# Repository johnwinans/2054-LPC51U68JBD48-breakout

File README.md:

# 2054-LPC51U68JBD48-breakout
LPC51U68JBD48 Breakout Board

Oops... I put the wrong URL on the Rev-1 release tag.  You can order Rev 1 of this board from OSH Park here: https://oshpark.com/shared_projects/a4fI5XNS (I receive no commission.)

Double-oops, there is no soldermask threaded between the pins of U1 in Rev-1.  This flaw is not a show-stopper.  It would have been nice to have.  

This has been fixed by reducing the solder mask expansion in Rev 1.1 to 1.8 mils.

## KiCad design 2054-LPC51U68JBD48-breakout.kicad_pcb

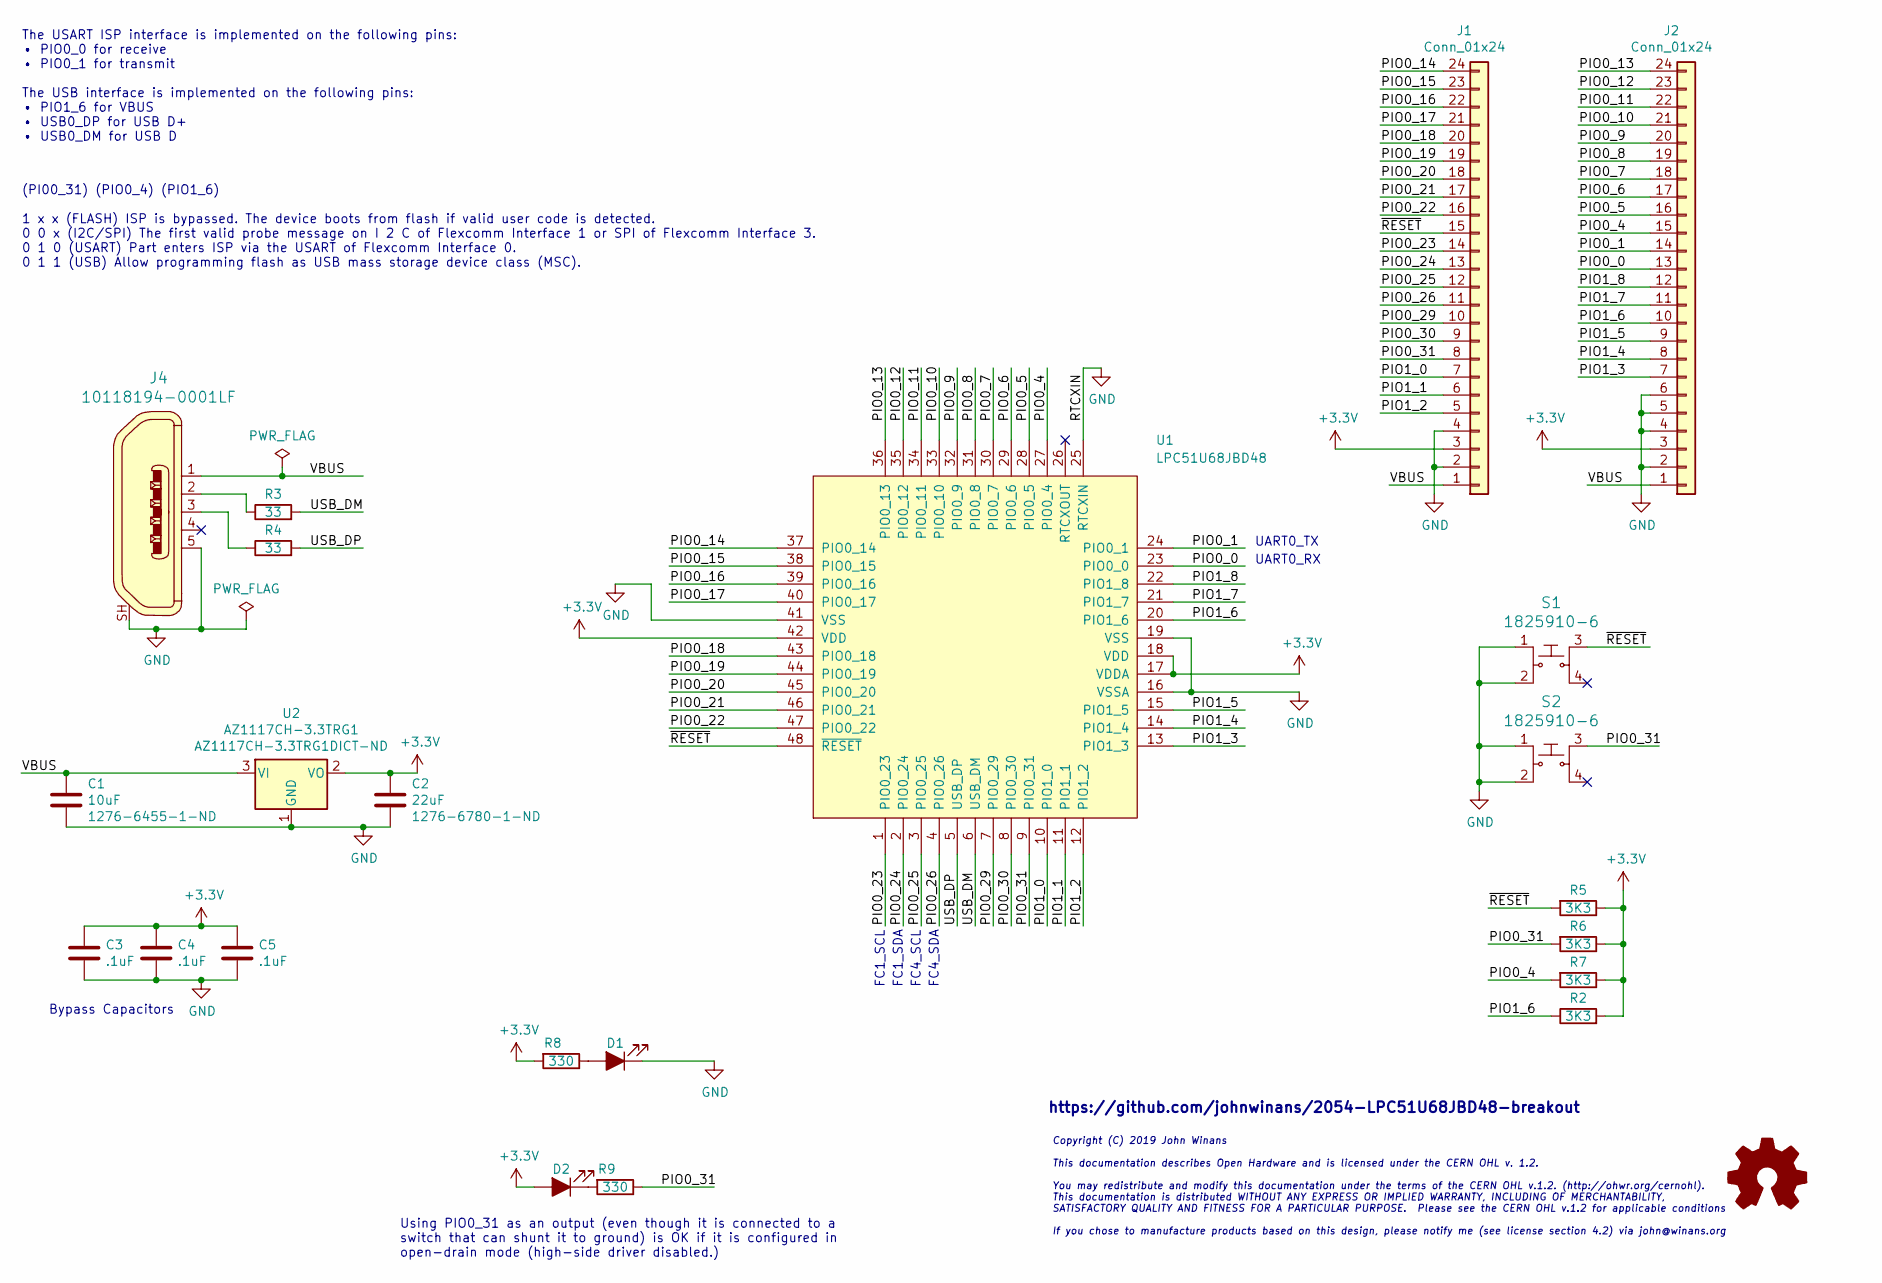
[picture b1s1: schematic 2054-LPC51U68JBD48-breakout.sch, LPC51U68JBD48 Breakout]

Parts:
C1: 10uF; C_0805_2012Metric_Pad1.15x1.40mm_HandSolder; digikey 1276-6455-1-ND
C2: 22uF; C_0805_2012Metric_Pad1.15x1.40mm_HandSolder; digikey 1276-6780-1-ND
C3, C4, C5: .1uF; C_0603_1608Metric_Pad1.05x0.95mm_HandSolder; digikey.com 445-6854-1-ND
D1, D2: LED_ALT; LED_0603_1608Metric_Pad1.05x0.95mm_HandSolder
J1, J2: Conn_01x24; PinHeader_1x24_P2.54mm_Vertical
J4: 10118194-0001LF; USB_Micro_B_Female_10118194-0001LF; MPN 10118194-0001LF; Digi-Key_PN 609-4618-1-ND
LOGO1: Logo_Open_Hardware_Small; OSHW-Symbol_6.7x6mm_SilkScreen
R2, R5, R6, R7: 3K3; R_0603_1608Metric_Pad1.05x0.95mm_HandSolder; digikey.com 311-100HRCT-ND
R3, R4: 33; R_0603_1608Metric_Pad1.05x0.95mm_HandSolder; digikey.com 311-100HRCT-ND
R8, R9: 330; R_0603_1608Metric_Pad1.05x0.95mm_HandSolder; digikey.com 311-1.00KHRCT-ND
S1, S2: 1825910-6; Switch_Tactile_THT_6x6mm; MPN 1825910-6; Digi-Key_PN 450-1650-ND
U1: LPC51U68JBD48; LQFP-48_7x7mm_P0.5mm
U2: AZ1117CH-3.3TRG1; SOT-223-3_TabPin2; digikey AZ1117CH-3.3TRG1DICT-ND

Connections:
+3V3: C2.1, C3.1, C4.1, C5.1, D2.2 (A), J1.3, J2.3, R2.2, R5.1, R6.1, R7.1, R8.2, U1.17 (VDDA), U1.18 (VDD), U1.42 (VDD), U2.2 (VO)
/PIO0_0: J2.13, U1.23 (PIO0_0)
/PIO0_1: J2.14, U1.24 (PIO0_1)
/PIO0_4: J2.15, R7.2, U1.27 (PIO0_4)
/PIO0_5: J2.16, U1.28 (PIO0_5)
/PIO0_6: J2.17, U1.29 (PIO0_6)
/PIO0_7: J2.18, U1.30 (PIO0_7)
/PIO0_8: J2.19, U1.31 (PIO0_8)
/PIO0_9: J2.20, U1.32 (PIO0_9)
/PIO0_10: J2.21, U1.33 (PIO0_10)
/PIO0_11: J2.22, U1.34 (PIO0_11)
/PIO0_12: J2.23, U1.35 (PIO0_12)
/PIO0_13: J2.24, U1.36 (PIO0_13)
/PIO0_14: J1.24, U1.37 (PIO0_14)
/PIO0_15: J1.23, U1.38 (PIO0_15)
/PIO0_16: J1.22, U1.39 (PIO0_16)
/PIO0_17: J1.21, U1.40 (PIO0_17)
/PIO0_18: J1.20, U1.43 (PIO0_18)
/PIO0_19: J1.19, U1.44 (PIO0_19)
/PIO0_20: J1.18, U1.45 (PIO0_20)
/PIO0_21: J1.17, U1.46 (PIO0_21)
/PIO0_22: J1.16, U1.47 (PIO0_22)
/PIO0_23: J1.14, U1.1 (PIO0_23)
/PIO0_24: J1.13, U1.2 (PIO0_24)
/PIO0_25: J1.12, U1.3 (PIO0_25)
/PIO0_26: J1.11, U1.4 (PIO0_26)
/PIO0_29: J1.10, U1.7 (PIO0_29)
/PIO0_30: J1.9, U1.8 (PIO0_30)
/PIO0_31: J1.8, R6.2, R9.1, S2.3, U1.9 (PIO0_31)
/PIO1_0: J1.7, U1.10 (PIO1_0)
/PIO1_1: J1.6, U1.11 (PIO1_1)
/PIO1_2: J1.5, U1.12 (PIO1_2)
/PIO1_3: J2.7, U1.13 (PIO1_3)
/PIO1_4: J2.8, U1.14 (PIO1_4)
/PIO1_5: J2.9, U1.15 (PIO1_5)
/PIO1_6: J2.10, R2.1, U1.20 (PIO1_6)
/PIO1_7: J2.11, U1.21 (PIO1_7)
/PIO1_8: J2.12, U1.22 (PIO1_8)
/USB_DM: R3.2, U1.6 (USB_DM)
/USB_DP: R4.2, U1.5 (USB_DP)
/VBUS: C1.1, J1.1, J2.1, J4.1, U2.3 (VI)
/~RESET~: J1.15, R5.2, S1.3, U1.48 (~RESET~)
GND: C1.2, C2.2, C3.2, C4.2, C5.2, D1.1 (K), J1.2, J1.4, J2.2, J2.4, J2.5, J2.6, J4.5, J4.SH, S1.1, S1.2, S2.1, S2.2, U1.16 (VSSA), U1.19 (VSS), U1.25 (RTCXIN), U1.41 (VSS), U2.1 (GND)
unnamed: D1.2 (A), R8.1
unnamed: D2.1 (K), R9.2
unnamed: J4.2, R3.1
unnamed: J4.3, R4.1

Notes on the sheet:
Bypass Capacitors
Copyright (C) 2019 John Winans This documentation describes Open Hardware and is licensed under the CERN OHL v. 1.2. You may redistribute and modify this documentation under the terms of the CERN OHL v.1.2. (http://ohwr.org/cernohl). This documentation is distributed WITHOUT ANY EXPRESS OR IMPLIED 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
The USART ISP interface is implemented on the following pins: • PIO0_0 for receive • PIO0_1 for transmit The USB interface is implemented on the following pins: • PIO1_6 for VBUS • USB0_DP for USB D+ • USB0_DM for USB D
(PI00_31) (PIO0_4) (PIO1_6) 1 x x (FLASH) ISP is bypassed. The device boots from flash if valid user code is detected. 0 0 x (I2C/SPI) The first valid probe message on I 2 C of Flexcomm Interface 1 or SPI of Flexcomm Interface 3. 0 1 0 (USART) Part enters ISP via the USART of Flexcomm Interface 0. 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
FC1_SCL
FC1_SDA
FC4_SCL
FC4_SDA
UART0_TX
UART0_RX
Using PIO0_31 as an output (even though it is connected to a switch that can shunt it to ground) is OK if it is configured in open-drain mode (high-side driver disabled.)
https://github.com/johnwinans/2054-LPC51U68JBD48-breakout

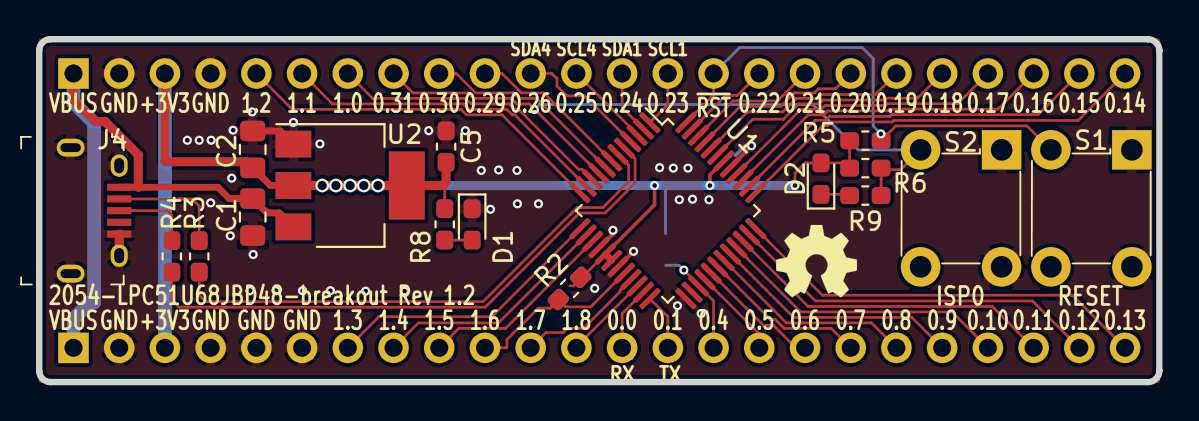
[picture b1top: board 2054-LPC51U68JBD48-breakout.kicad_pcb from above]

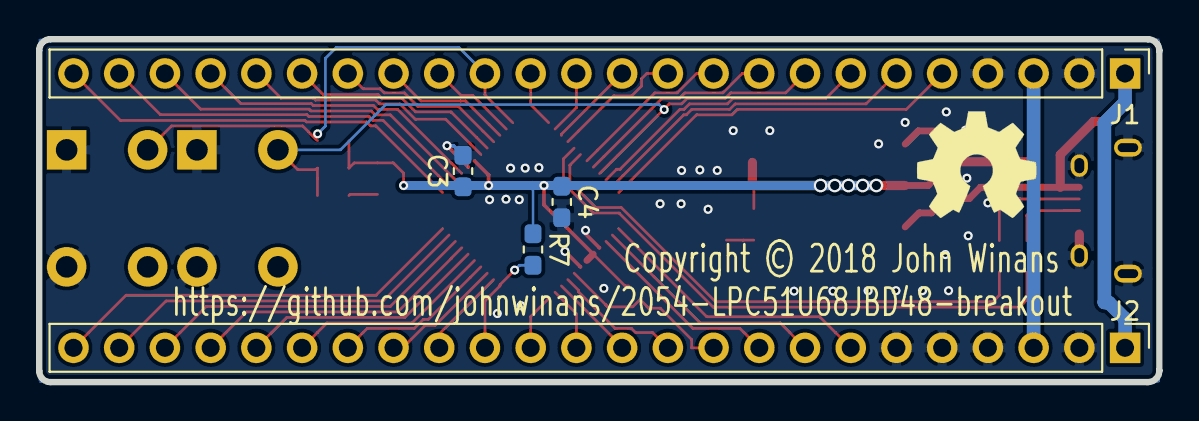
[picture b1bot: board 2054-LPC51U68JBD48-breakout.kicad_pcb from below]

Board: 2 copper layers, 62.2 x 19.0 mm, 23 parts (6 on the bottom side), 47 nets.

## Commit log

2019-06-12 Initial project import
2019-06-12 Added a picture.
2019-06-23 Add note about the soldermask around U1 pins.
2019-06-23 Reduce soldermask expansion to 1.8mil
2019-07-07 CHanged Rev number on schematic & PCB.
2021-07-07 Added the cache.lib in case anyone needs it.

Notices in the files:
2054-LPC51U68JBD48-breakout.kicad_pcb:
Copyright © 2018 John Winans
2054-LPC51U68JBD48-breakout.sch:
If you chose to manufacture products based on this design, please notify me (see license section 4.2) via john@winans.org
